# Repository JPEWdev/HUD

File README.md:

# HUD
A vehicular Heads Up Display based on an Atmel

## Dependencies
This software depends uses avr-gcc and avr-libc to compile. To flash the sofware onto the device, you will need avrdude installed and an ISP programmer. You may need to tweak the make file if you use a programmer other than the AVRISP MkII.

## Compiling
To compile the software, simply run `make`

## Installing
To install the software onto the device, run `make writeflash`.

If you have a fresh part that has never been programmed before, you will need to program the fuse bits before you can program the main software. To do this, run `make writefuses`. This command is clocked at a low speed to ensure that it will work when the AVR is running off of either its internal oscialltor or the external crystal. This is fine, because the command is only writing the fuse bits, which doesn't take long

## Assembly
The HUD.brd file in the respository can be used to fabricate the main board. You can order all of the parts except for the ELM329 chip from [Digikey](www.digikey.com) using the [BOM.txt](./misc/BOM.txt) file (you can directly import this on the [DigiKey website](https://www.digikey.com/classic/ordering/addpart.aspx), use the "Upload to Cart" option). You can order the ELM329 from [ELM's website](https://www.elmelectronics.com/ic/elm329/)

Total cost for PCB fabrication and all components should be less than $200 USD.

## Display
The display that should be connected to the main board is the Noritake GU140X16G-7003 Vacuum Fluorescent Display. You will need to solder the jumper on the back to put the display into Synchronus Serial Mode (Short jumper J2 on the back of the display). Pins 1-6 on the 6 pin header should be wired to pins 1-6 on the display header of the main board in the same order (i.e. pin 1 to pin 1). Pin 1 on the display board header is the closest to the bottom of the board. Pin 7 on the main board is not used with the VFD display.

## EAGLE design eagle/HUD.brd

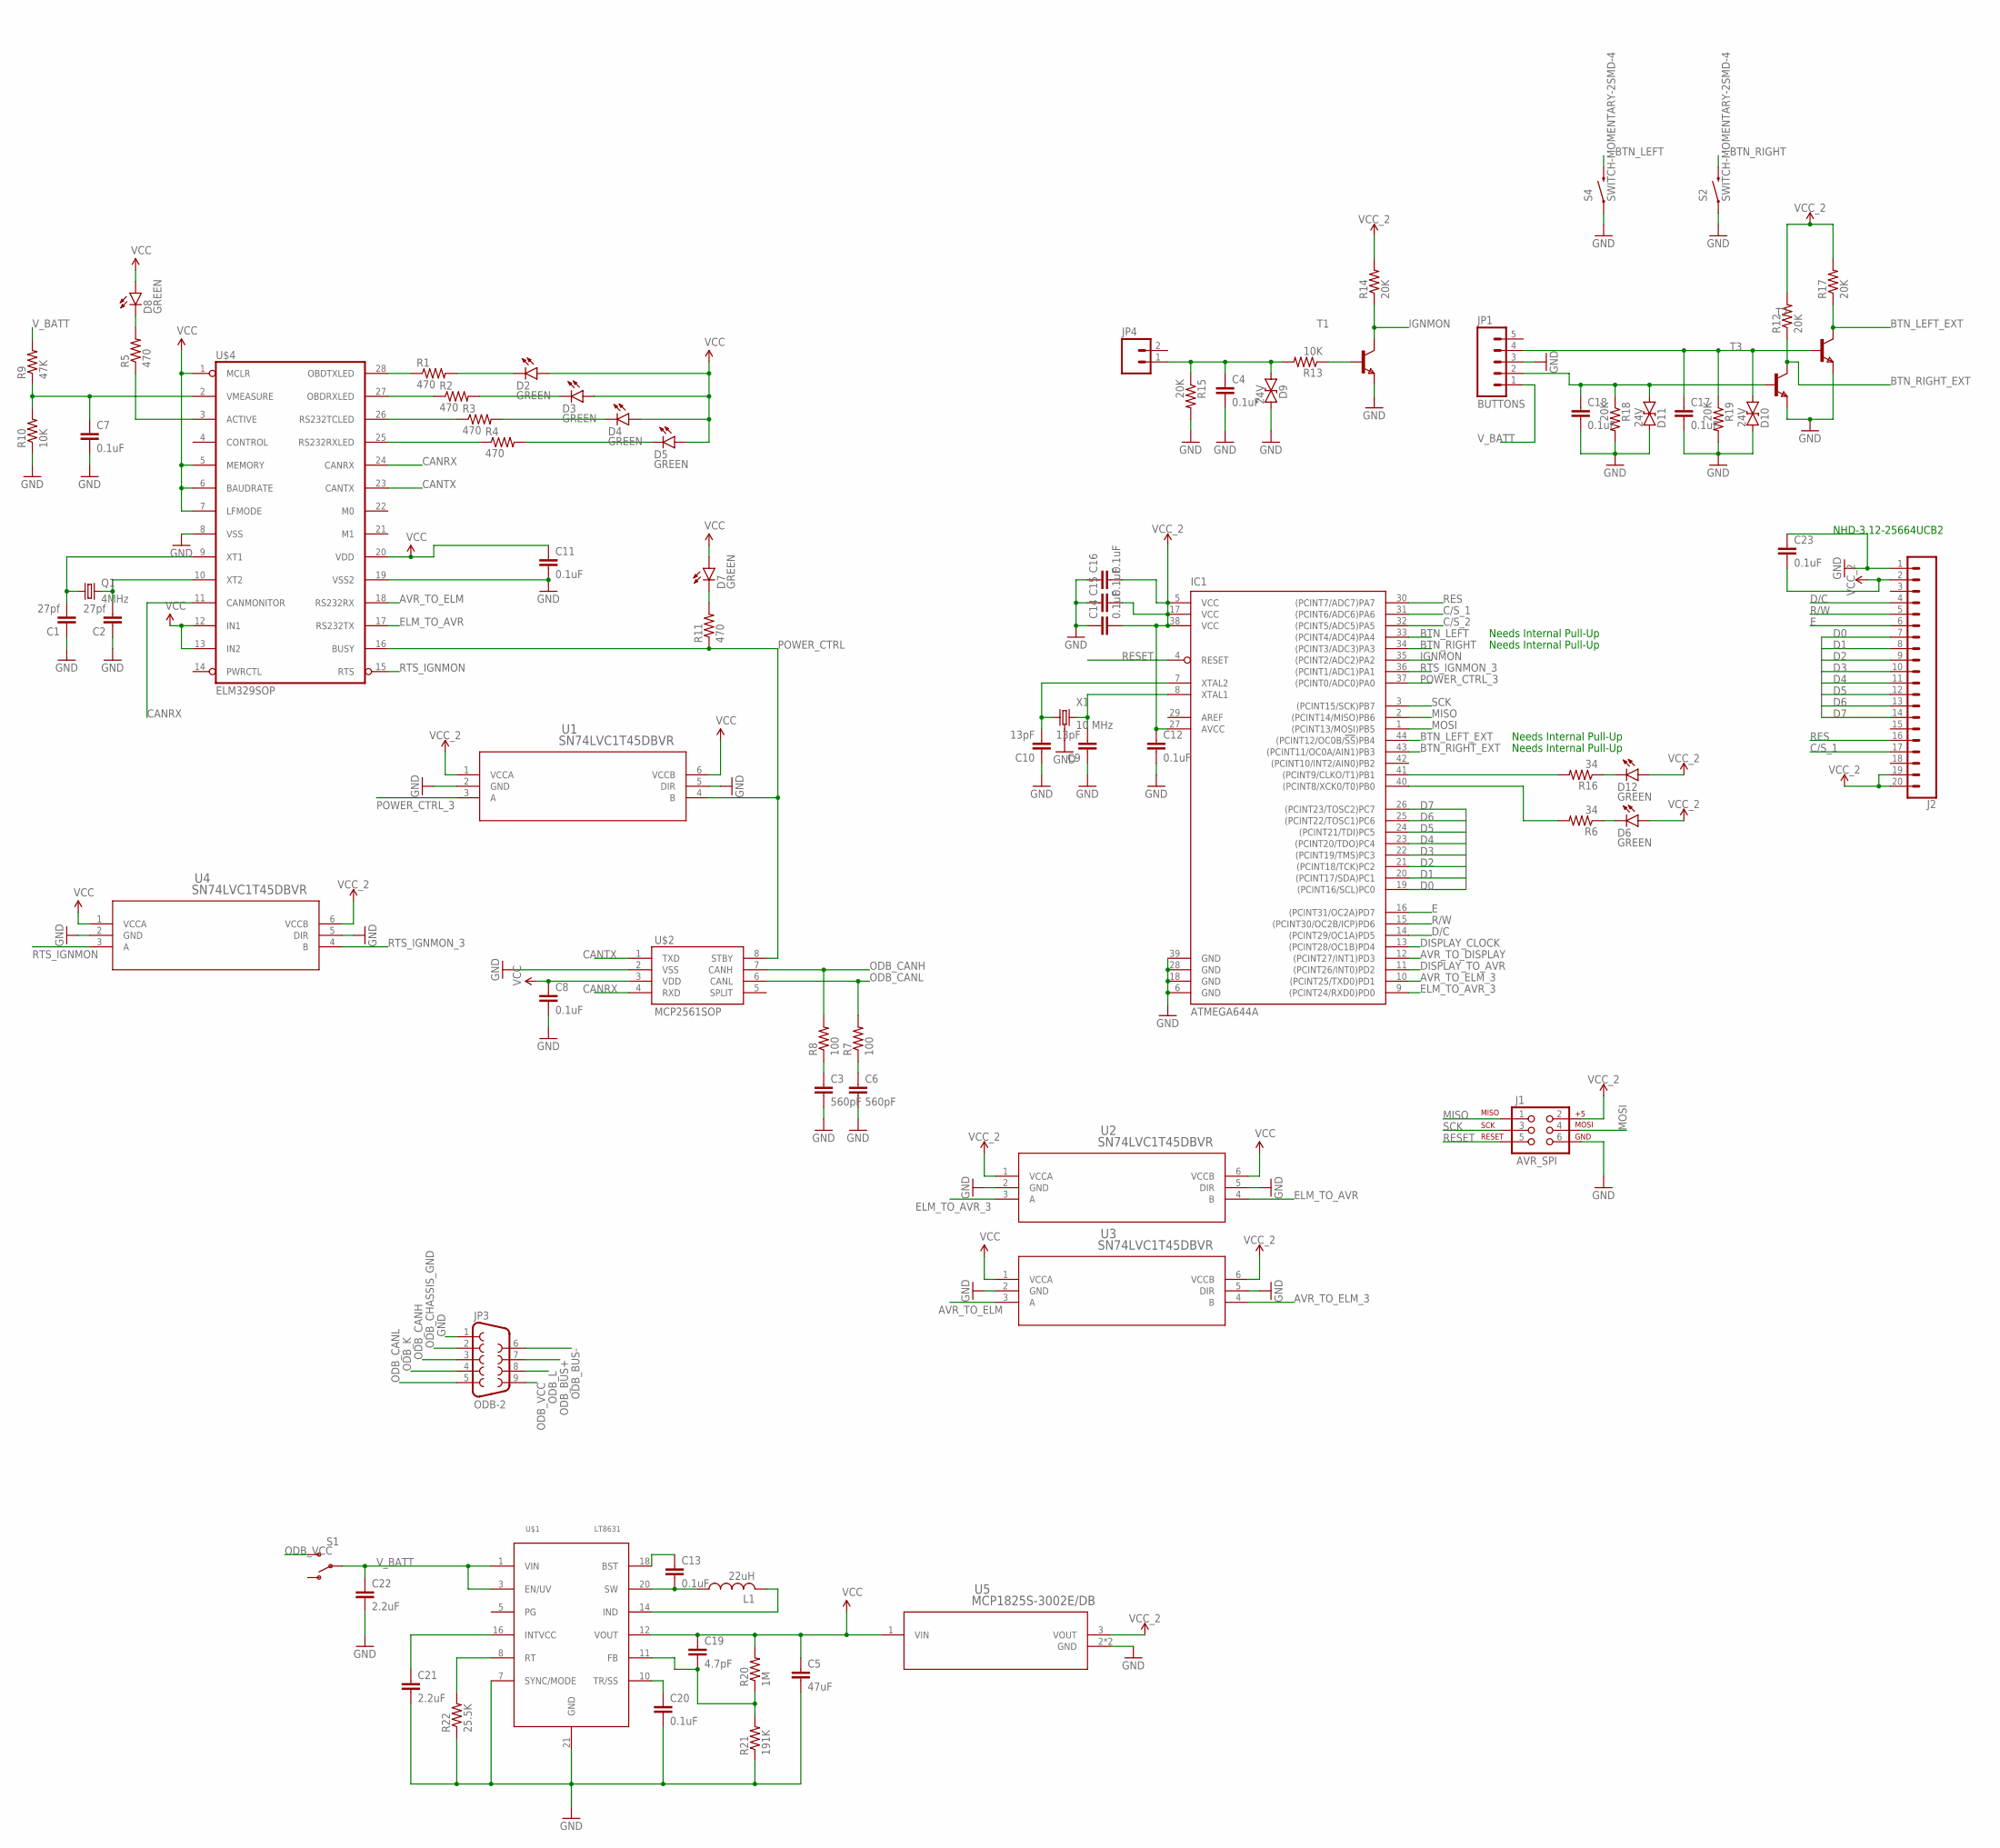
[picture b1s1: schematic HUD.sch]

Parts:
C1, C2: 27pf; 0603-CAP
C3, C6: 560pF; 0603-CAP
C4, C7, C8, C11, C12, C13, C14, C15, C16, C17, C18, C20, C23: 0.1uF; 0603-CAP
C5: 47uF; C1206
C9, C10: 13pF; 0603-CAP
C19: 4.7pF; 0603-CAP
C21: 2.2uF; 0603-CAP
C22: 2.2uF; C1206
D2, D3, D4, D5, D6, D7, D8, D12: GREEN; LED-1206
D9, D10, D11: 24V; SOD-123
IC1: ATMEGA644A; TQFP44
J1: AVR_SPI; 2X3
J2: CONN_20LOCK; 1X20_LOCK
JP1: BUTTONS; 1X05_LOCK
JP3: ODB-2; DB9_MALE
JP4: M02LOCK; 1X02_LOCK
L1: 22uH; PIS2816
Q1: 4MHz; SM49
R1, R2, R3, R4, R5, R11: 470; 0603-RES
R6, R16: 34; 0603-RES
R7, R8: 100; 0603-RES
R9: 47K; 0603-RES
R10, R13: 10K; 0603-RES
R12, R14, R15, R17, R18, R19: 20K; 0603-RES
R20: 1M; 0603-RES
R21: 191K; 0603-RES
R22: 25.5K; 0603-RES
S1: SWITCH-SPDTPTH; SWITCH-SPDT
S2, S4: SWITCH-MOMENTARY-2SMD-4; TACTILE_SWITCH_TALL
T1, T2, T3: NPNSOT323; SOT323
U1, U2, U3, U4: SN74LVC1T45DBVR; DBV6
U5: MCP1825S-3002E/DB; SOT-223_3MC
U$1: LT8631; TSSOP20
U$2: MCP2561SOP; SO08
U$4: ELM329SOP; SO28W
X1: 10 MHz; CRYSTAL-SMD-3.2X2.5

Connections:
AVR_TO_DISPLAY: IC1.12 ((PCINT27/INT1)PD3)
AVR_TO_ELM: U3.3 (A), U$4.18 (RS232RX)
AVR_TO_ELM_3: IC1.10 ((PCINT25/TXD0)PD1), U3.4 (B)
BTN_LEFT: IC1.33 ((PCINT4/ADC4)PA4), S4.B2 (2)
BTN_LEFT_EXT: IC1.44 ((PCINT12/OC0B/!SS!)PB4), R17.1, T2.1 (C)
BTN_RIGHT: IC1.34 ((PCINT3/ADC3)PA3), S2.B2 (2)
BTN_RIGHT_EXT: IC1.43 ((PCINT11/OC0A/AIN1)PB3), R12.1, T3.1 (C)
C/S_1: IC1.31 ((PCINT6/ADC6)PA6), J2.17
C/S_2: IC1.32 ((PCINT5/ADC5)PA5)
CANRX: U$2.4 (RXD), U$4.11 (CANMONITOR), U$4.24 (CANRX)
CANTX: U$2.1 (TXD), U$4.23 (CANTX)
D0: IC1.19 ((PCINT16/SCL)PC0), J2.7
D1: IC1.20 ((PCINT17/SDA)PC1), J2.8
D2: IC1.21 ((PCINT18/TCK)PC2), J2.9
D3: IC1.22 ((PCINT19/TMS)PC3), J2.10
D4: IC1.23 ((PCINT20/TDO)PC4), J2.11
D5: IC1.24 ((PCINT21/TDI)PC5), J2.12
D6: IC1.25 ((PCINT22/TOSC1)PC6), J2.13
D7: IC1.26 ((PCINT23/TOSC2)PC7), J2.14
D/C: IC1.14 ((PCINT29/OC1A)PD5), J2.4
DISPLAY_CLOCK: IC1.13 ((PCINT28/OC1B)PD4)
DISPLAY_TO_AVR: IC1.11 ((PCINT26/INT0)PD2)
E: IC1.16 ((PCINT31/OC2A)PD7), J2.6
ELM_TO_AVR: U2.4 (B), U$4.17 (RS232TX)
ELM_TO_AVR_3: IC1.9 ((PCINT24/RXD0)PD0), U2.3 (A)
GND: C1.1, C2.1, C3.2, C4.2, C5.2, C6.2, C7.2, C8.2, C9.1, C10.1, C11.2, C12.2, C14.1, C15.1, C16.1, C17.2, C18.2, C20.2, C21.2, C22.2, C23.1, D9.C, D10.C, D11.C, IC1.6 (GND), IC1.18 (GND), IC1.28 (GND), IC1.39 (GND), J1.6, J2.1, JP1.3, JP3.1, R10.1, R15.2, R18.2, R19.2, R21.1, R22.1, S2.A2 (1), S4.A2 (1), T1.3 (E), T2.3 (E), T3.3 (E), U1.2 (GND), U1.5 (DIR), U2.2 (GND), U2.5 (DIR), U3.2 (GND), U3.5 (DIR), U4.2 (GND), U4.5 (DIR), U5.2 (GND), U5.4 (GND), U$1.7 (SYNC/MODE), U$1.21 (GND), U$2.2 (VSS), U$4.8 (VSS), U$4.19 (VSS2), X1.2 (3), X1.4 (3)
IGNMON: IC1.35 ((PCINT2/ADC2)PA2), R14.1, T1.1 (C)
MISO: IC1.2 ((PCINT14/MISO)PB6), J1.1
MOSI: IC1.1 ((PCINT13/MOSI)PB5), J1.4
unnamed: D12.C, R16.1
unnamed: D7.C, R11.2
unnamed: C4.1, D9.A, JP4.1, R13.2, R15.1
unnamed: IC1.40 ((PCINT8/XCK0/T0)PB0), R6.2
unnamed: R13.1, T1.2 (B)
unnamed: L1.2, U$1.14 (IND)
unnamed: R1.1, U$4.28 (OBDTXLED)
unnamed: IC1.41 ((PCINT9/CLKO/T1)PB1), R16.2
unnamed: R2.1, U$4.27 (OBDRXLED)
unnamed: D6.C, R6.1
unnamed: R3.1, U$4.26 (RS232TCLED)
unnamed: C17.1, D10.A, JP1.4, R19.1, T2.2 (B)
unnamed: C18.1, D11.A, JP1.2, R18.1, T3.2 (B)
unnamed: R4.1, U$4.25 (RS232RXLED)
unnamed: C1.2, Q1.1, U$4.9 (XT1)
unnamed: C2.2, Q1.2, U$4.10 (XT2)
unnamed: R5.1, U$4.3 (ACTIVE)
unnamed: D2.C, R1.2
unnamed: D3.C, R2.2
unnamed: D4.C, R3.2
unnamed: D5.C, R4.2
unnamed: D8.C, R5.2
unnamed: C13.2, L1.1, U$1.20 (SW)
unnamed: C13.1, U$1.18 (BST)
unnamed: C20.1, U$1.10 (TR/SS)
unnamed: C19.2, R20.1, R21.2, U$1.11 (FB)
unnamed: C3.1, R8.1
unnamed: C6.1, R7.1
unnamed: C21.1, U$1.16 (INTVCC)
unnamed: C7.1, R9.1, R10.2, U$4.2 (VMEASURE)
unnamed: R22.2, U$1.8 (RT)
unnamed: C10.2, IC1.7 (XTAL2), X1.3 (1)
unnamed: C9.2, IC1.8 (XTAL1), X1.1 (2)
ODB_BUS+: JP3.7
ODB_BUS-: JP3.6
ODB_CANH: JP3.3, R8.2, U$2.7 (CANH)
ODB_CANL: JP3.5, R7.2, U$2.6 (CANL)
ODB_CHASSIS_GND: JP3.2
ODB_K: JP3.4
ODB_L: JP3.8
ODB_VCC: JP3.9, S1.3 (S)
POWER_CTRL: R11.1, U1.4 (B), U$2.8 (STBY), U$4.16 (BUSY)
POWER_CTRL_3: IC1.37 ((PCINT0/ADC0)PA0), U1.3 (A)
R/W: IC1.15 ((PCINT30/OC2B/ICP)PD6), J2.5
RES: IC1.30 ((PCINT7/ADC7)PA7), J2.16
RESET: IC1.4 (RESET), J1.5
RTS_IGNMON: U4.3 (A), U$4.15 (RTS)
RTS_IGNMON_3: IC1.36 ((PCINT1/ADC1)PA1), U4.4 (B)
SCK: IC1.3 ((PCINT15/SCK)PB7), J1.3
VCC: C5.1, C8.1, C11.1, C19.1, D2.A, D3.A, D4.A, D5.A, D7.A, D8.A, R20.2, U1.6 (VCCB), U2.6 (VCCB), U3.1 (VCCA), U4.1 (VCCA), U5.1 (VIN), U$1.12 (VOUT), U$2.3 (VDD), U$4.1 (MCLR), U$4.5 (MEMORY), U$4.6 (BAUDRATE), U$4.7 (LFMODE), U$4.12 (IN1), U$4.13 (IN2), U$4.20 (VDD)
VCC_2: C12.1, C14.2, C15.2, C16.2, C23.2, D6.A, D12.A, IC1.5 (VCC), IC1.17 (VCC), IC1.27 (AVCC), IC1.38 (VCC), J1.2, J2.2, J2.19, J2.20, R12.2, R14.2, R17.2, U1.1 (VCCA), U2.1 (VCCA), U3.6 (VCCB), U4.6 (VCCB), U5.3 (VOUT)
V_BATT: C22.1, JP1.1, R9.2, S1.2, U$1.1 (VIN), U$1.3 (EN/UV)

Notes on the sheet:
Needs Internal Pull-Up
NHD-3.12-25664UCB2

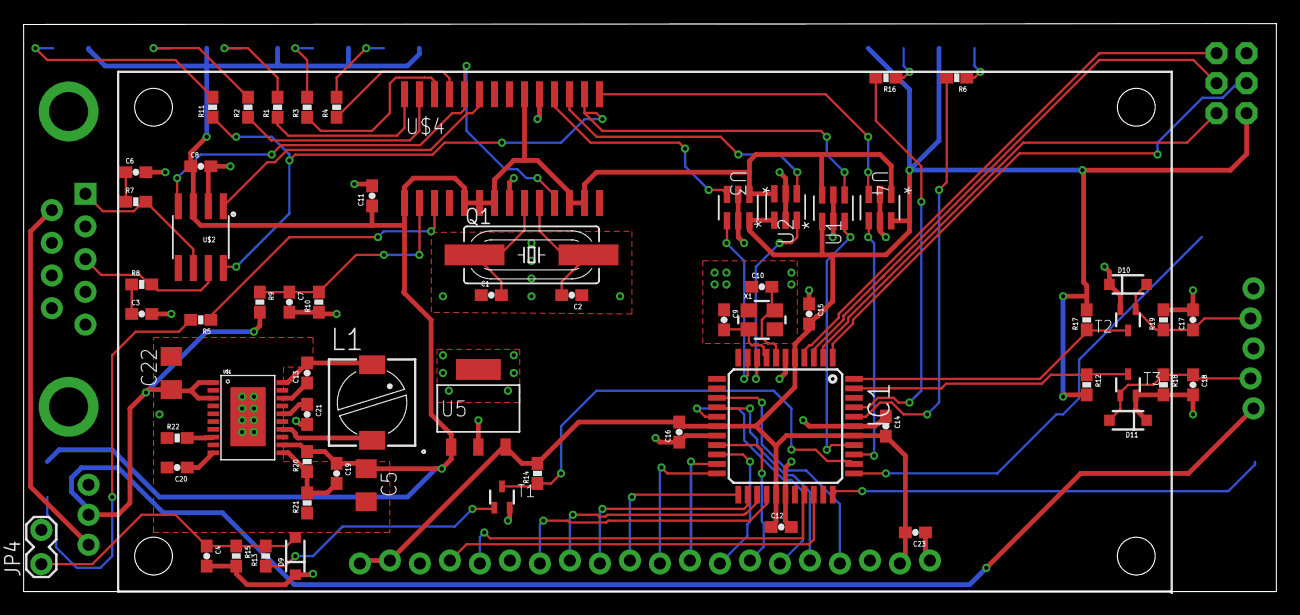
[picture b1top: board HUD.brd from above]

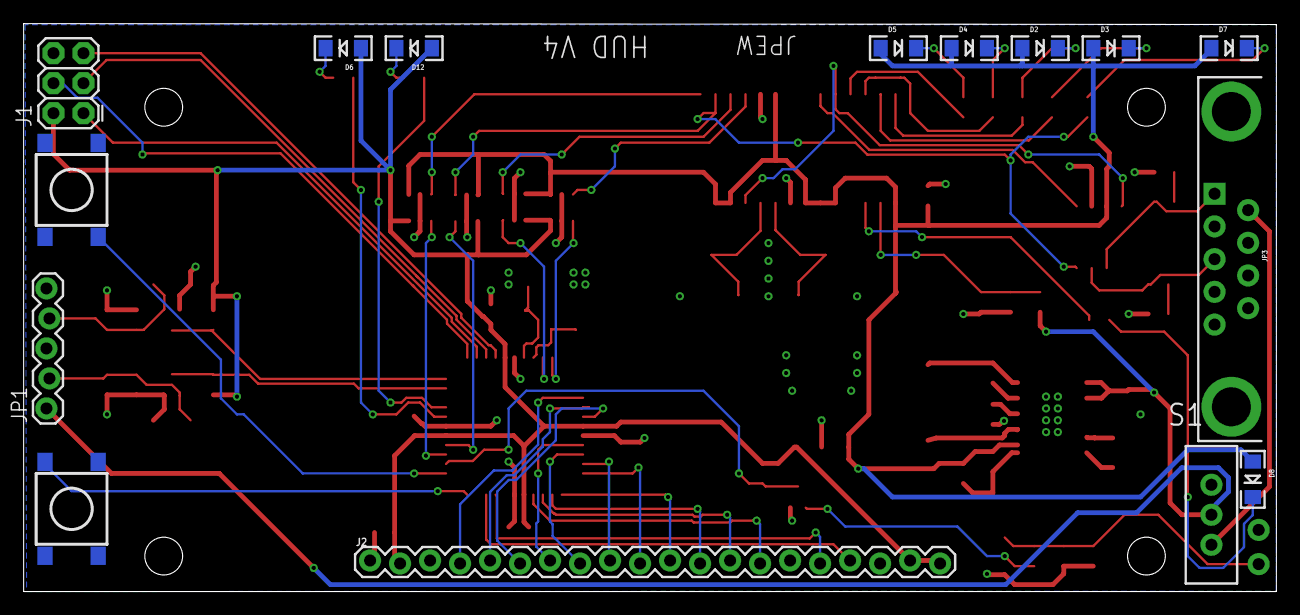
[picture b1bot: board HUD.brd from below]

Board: 2 copper layers, 106.1 x 48.1 mm, 79 parts (15 on the bottom side), 72 nets.

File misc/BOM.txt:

Qty	Value	Device	Package	Parts	Digikey PN	Link
13	0.1uF	560PF-50V-5%(0603)	0603-CAP	C4  C7  C8  C11  C12  C13  C14  C15  C16  C17  C18  C20  C23	490-1532-1-ND	http://www.digikey.com/short/3f834t
2	13pF	560PF-50V-5%(0603)	0603-CAP	C9  C10	490-1406-1-ND	http://www.digikey.com/short/3ft1m7
1	2.2uF	560PF-50V-5%(0603)	0603-CAP	C21	445-6933-1-ND	https://www.digikey.com/short/qq177z
2	27pf	560PF-50V-5%(0603)	0603-CAP	C1  C2	399-7888-1-ND	http://www.digikey.com/short/3ft149
1	4.7pF	560PF-50V-5%(0603)	0603-CAP	C19	712-1172-1-ND 	https://www.digikey.com/short/qqv1ft
2	560pF	560PF-50V-5%(0603)	0603-CAP	C3  C6	1276-1278-1-ND 	https://www.digikey.com/short/qqv1fh
1	ATMEGA644A	ATMEGA644A	TQFP44	IC1	ATMEGA644PA-AU-ND	http://www.digikey.com/short/3ft1m9
1	AVR_SPI	AVR_SPI_PRG_6PTH	2X3	J1	952-2121-ND	https://www.digikey.com/short/qq1775
1	47uF	C-EUC1206	C1206	C5	490-8337-1-ND 	https://www.digikey.com/short/qqv12q
1	2.2uF	C-EUC1206	C1206	C22	490-3368-1-ND	https://www.digikey.com/short/q7qn09
1	10 MHz	CRYSTAL-GROUNDED3.2X2.5	CRYSTAL-SMD-3.2X2.5	X1	887-1791-1-ND 	http://www.digikey.com/short/qcp8f8
1	4MHz	CRYSTALSM49	SM49	Q1	535-9085-1-ND	https://www.digikey.com/short/qqv124
1	ODB-2	DB9MALE	DB9_MALE	JP3	182-809ME-ND	https://www.digikey.com/short/qqv122
3	24V	DIODE-TVS16V	SOD-123	D9  D10  D11	F5823CT-ND 	https://www.digikey.com/short/qqv1w7
1	ELM329SOP	ELM329SOP	SO28W	U$4		
1	22uH	L-USPIS2816	PIS2816	L1	513-1532-1-ND	https://www.digikey.com/short/qqv1nr
8	GREEN	LED-GREENLARGE	LED-1206	D2  D3  D4  D5  D6  D7  D8  D12	404-1046-1-ND	http://www.digikey.com/short/3ft1m4
1	LT8631	LT8631	TSSOP20	U$1	LT8631IFE#PBF-ND	https://www.digikey.com/short/qqv1dj
1	BUTTONS	M05LOCK	1X05_LOCK	JP1		
1	MCP1825S-3002E/DB	MCP1825S-3002E/DB	SOT-223_3MC	U5	MCP1825ST-3302E/DBDKR-ND	https://www.digikey.com/short/qqv103
1	MCP2561SOP	MCP2561SOP	SO08	U$2	MCP2561-E/SN-ND	http://www.digikey.com/short/3f83mn
3		NPNSOT323	SOT323	T1  T2  T3	MMST3904-FDICT-ND	https://www.digikey.com/short/3w58f5
2	100	RESISTOR0603-RES	0603-RES	R7  R8	311-100HRCT-ND	https://www.digikey.com/short/3w9t3m
2	10K	RESISTOR0603-RES	0603-RES	R10  R13	311-10KGRCT-ND	https://www.digikey.com/short/3w9t3d
1	191K	RESISTOR0603-RES	0603-RES	R21	P191KDBCT-ND	https://www.digikey.com/short/qqv1vz
1	1M	RESISTOR0603-RES	0603-RES	R20	A119955CT-ND	https://www.digikey.com/short/qqv1v9
6	20K	RESISTOR0603-RES	0603-RES	R12  R14  R15  R17  R18  R19	RR08P20.0KDCT-ND	https://www.digikey.com/short/qqv112
1	25.5K	RESISTOR0603-RES	0603-RES	R22	311-25.5KHRCT-ND	https://www.digikey.com/short/qqv11v
2	34	RESISTOR0603-RES	0603-RES	R6  R16	311-34.0HRCT-ND	https://www.digikey.com/short/qq1ccm
6	470	RESISTOR0603-RES	0603-RES	R1  R2  R3  R4  R5  R11	RR08P470DCT-ND	https://www.digikey.com/short/qq1cc5
1	47K	RESISTOR0603-RES	0603-RES	R9	P47KDBCT-ND	https://www.digikey.com/short/qq1c12
4	SN74LVC1T45DBVR	SN74LVC1T45DBVR	DBV6	U1  U2  U3  U4	296-16843-1-ND	https://www.digikey.com/short/qq1c10
2	SWITCH-MOMENTARY-2SMD-4	SWITCH-MOMENTARY-2SMD-4	TACTILE_SWITCH_TALL	S2  S4	CKN9112CT-ND	http://www.digikey.com/short/3f83mf
1		SWITCH-SPDTPTH	SWITCH-SPDT	S1	360-2133-ND	http://www.digikey.com/short/3f83mh
1		LCD OLED GRAPHIC 256 X 64 BLUE			NHD-3.12-25664UCB2-ND	https://www.digikey.com/short/q78884

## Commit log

2017-04-24 Initial code commit
    Add all the initial code and eagle files for the HUD
2017-04-25 Add BOM
    Adds Bill of Materials
2017-04-25 Rename BOM
    Renames the BOM file to be compatible with DigiKey's website
2017-04-29 Remove PID size table
    Removes the PID size table from the ELM driver and instead passes the
    size along in the callback
2017-04-29 Add diagnostic page for showing PID values
    Adds a page that shows the hex value for all available PIDs
2017-04-29 Fix Fuel Economy showing up as "nan"
    Fuel economy would sometime show up as "nan". This was when a Mass
    Airflow Rate of 0 (typically when the engine was not running) causing a
    divide-by-zero condition to occur. Once this happened, there was no
    recovery because any operation done to a float NaN continues to result
    in NaN
2018-01-01 V4 Schematic and board layout
2019-05-30 Add engine coolant temp and oil temp
2019-05-30 Fix compiler warning
    Fixes a compiler warning about a string format buffer overrun.

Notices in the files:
parts and their libraries:
SparkFun-Capacitors: Licensing: Creative Commons ShareAlike 4.0 International - https://creativecommons.org/licenses/by-sa/4.0
